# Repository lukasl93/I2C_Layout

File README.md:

# I2C_Layout
Jolla Phone Breakoutboard PCB Layout

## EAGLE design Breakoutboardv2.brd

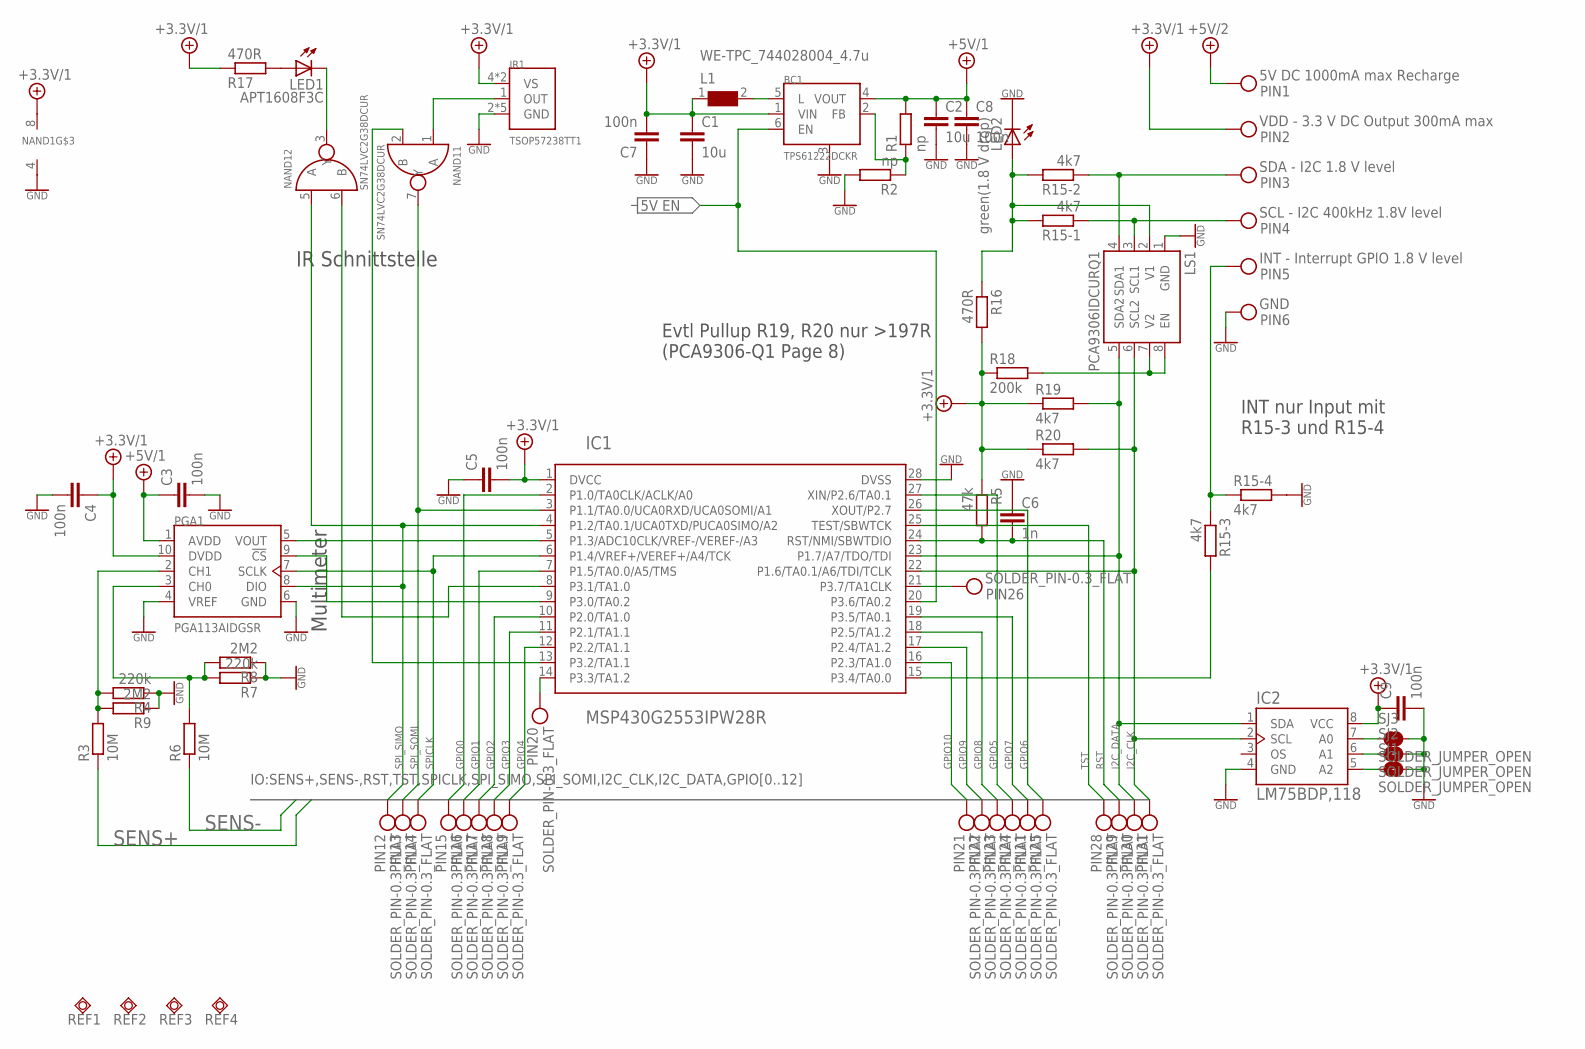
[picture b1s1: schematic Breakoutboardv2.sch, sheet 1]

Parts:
BC1: TPS61222DCKR; SOP65P210X110-6L
C1, C2: 10u; CAPC2012X95N
C3, C4, C5, C7, C8, C9: 100n; CAPC1608X90L
C6: 1n; CAPC1608X90L
IC1: MSP430G2553IPW28R; SOP65P640X120-28L
IC2: LM75BDP,118; SOP65P400X130-8L
IR1: TSOP57238TT1; TSOP572
L1: WE-TPC_744028004_4.7u; WE-TPC_2811/2813
LED1: APT1608F3C; LED-0603
LED2: green(1.8 V drop); LED-0603
LS1: PCA9306IDCURQ1; SOP50P310X90-8L
NAND1: SN74LVC2G38DCUR; SOP50P310X90-8L
PGA1: PGA113AIDGSR; SOP50P490X110-10L
PIN1: 5V DC 1000mA max Recharge; SOLDER_PIN_1_FLAT
PIN2: VDD - 3.3 V DC Output 300mA max; SOLDER_PIN_1_FLAT
PIN3: SDA - I2C 1.8 V level; SOLDER_PIN_1_FLAT
PIN4: SCL - I2C 400kHz 1.8V level; SOLDER_PIN_1_FLAT
PIN5: INT - Interrupt GPIO 1.8 V level; SOLDER_PIN_1_FLAT
PIN6: GND; SOLDER_PIN_1_FLAT
PIN11, PIN12, PIN13, PIN14, PIN15, PIN16, PIN17, PIN18, PIN19, PIN20, PIN21, PIN22, PIN23, PIN24, PIN25, PIN26, PIN28, PIN29, PIN30, PIN31: SOLDER_PIN-0.3_FLAT; SOLDER_PIN_0.3_FLAT
R1, R2: np; RESC1608X45L
R3, R6: 10M; RESC1608X45L
R4, R7: 220k; RESC1608X45L
R5: 47k; RESC1608X45L
R8, R9: 2M2; RESC1608X45L
R15: 4k7; R_ARRAY_742
R16, R17: 470R; RESC1608X45L
R18: 200k; RESC1608X45L
R19, R20: 4k7; RESC1608X45L
REF1, REF2, REF3, REF4: PCB-REF-1.27; PCB-REF
SJ1, SJ2, SJ3: SOLDER_JUMPER_OPEN; SJ-O

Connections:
5VEN: BC1.6 (EN), IC1.20 (P3.6/TA0.2)
+3.3V/1: BC1.1 (VIN), C1.1, C4.1, C5.2, C7.2, C9.1, IC1.1 (DVCC), IC2.8 (VCC), IR1.4 (VS), IR1.5 (VS), L1.1, NAND1.8 (VDD), PGA1.10 (DVDD), PIN2._, R5.1, R16.2, R17.1, R18.1, R19.1, R20.1; also elsewhere on the board
+5V/1: BC1.4 (VOUT), C2.1, C3.1, C8.1, PGA1.1 (AVDD), R1.2; also elsewhere on the board
+5V/2: PIN1._; also elsewhere on the board
CS_PGA: IC1.9 (P3.0/TA0.2), PGA1.9 (!CS)
GND: BC1.3 (GND), C1.2, C2.2, C3.2, C4.2, C5.1, C6.1, C7.1, C8.2, C9.2, IC1.28 (DVSS), IC2.4 (GND), IR1.2 (GND), IR1.3 (GND), IR1.6 (GND), IR1.7 (GND), IR1.8 (GND), LED2.C, LS1.1 (GND), NAND1.4 (GND), PGA1.4 (VREF), PGA1.6 (GND), PIN6._, R2.2, R4.1, R7.1, R8.1, R9.1, R15.5 (2), SJ1.2, SJ2.2, SJ3.2; also elsewhere on the board
GPIO0: IC1.2 (P1.0/TA0CLK/ACLK/A0), PIN15._; also elsewhere on the board
GPIO1: IC1.7 (P1.5/TA0.0/A5/TMS), PIN16._; also elsewhere on the board
GPIO2: IC1.10 (P2.0/TA1.0), PIN17._; also elsewhere on the board
GPIO3: IC1.11 (P2.1/TA1.1), PIN18._; also elsewhere on the board
GPIO4: IC1.12 (P2.2/TA1.1), PIN19._; also elsewhere on the board
GPIO5: IC1.27 (XIN/P2.6/TA0.1), PIN24._; also elsewhere on the board
GPIO6: IC1.26 (XOUT/P2.7), PIN25._; also elsewhere on the board
GPIO7: IC1.19 (P3.5/TA0.1), PIN11._; also elsewhere on the board
GPIO8: IC1.18 (P2.5/TA1.2), PIN23._; also elsewhere on the board
GPIO9: IC1.17 (P2.4/TA1.2), PIN22._; also elsewhere on the board
GPIO10: IC1.16 (P2.3/TA1.0), PIN21._; also elsewhere on the board
I2C_CLK: IC1.22 (P1.6/TA0.1/A6/TDI/TCLK), IC2.2 (SCL), LS1.6 (SCL2), PIN31._, R20.2; also elsewhere on the board
I2C_DATA: IC1.23 (P1.7/A7/TDO/TDI), IC2.1 (SDA), LS1.5 (SDA2), PIN30._, R19.2; also elsewhere on the board
INT_JOLLA: IC1.15 (P3.4/TA0.0), R15.6 (2)
IR-R_CONT: IC1.13 (P3.2/TA1.1), NAND1.2 (B)
IR-T_CONT: IC1.8 (P3.1/TA1.0), NAND1.6 (B)
unnamed: BC1.2 (FB), R1.1, R2.1
unnamed: BC1.5 (L), L1.2
unnamed: IC2.7 (A0), SJ3.1
unnamed: PGA1.2 (CH1), R3.2, R4.2, R9.2
unnamed: IC2.6 (A1), SJ2.1
unnamed: IC1.14 (P3.3/TA1.2), PIN20._
unnamed: PGA1.3 (CH0), R6.2, R7.2, R8.2
unnamed: IC2.5 (A2), SJ1.1
unnamed: IC1.21 (P3.7/TA1CLK), PIN26._
unnamed: LED1.A, R17.2
unnamed: PIN5._, R15.3 (1), R15.4 (1)
unnamed: LED2.A, LS1.2 (V1), R15.7 (2), R15.8 (2), R16.1
unnamed: IR1.1 (OUT), NAND1.1 (A)
unnamed: LED1.C, NAND1.3 (Y)
unnamed: LS1.4 (SDA1), PIN3._, R15.2 (1)
unnamed: LS1.7 (V2), LS1.8 (EN), R18.2
unnamed: LS1.3 (SCL1), PIN4._, R15.1
RST: C6.2, IC1.24 (RST/NMI/SBWTDIO), PIN29._, R5.2; also elsewhere on the board
SENS+: R3.1; also elsewhere on the board
SENS-: R6.1; also elsewhere on the board
SPICLK: IC1.6 (P1.4/VREF+/VEREF+/A4/TCK), PGA1.7 (SCLK), PIN14._; also elsewhere on the board
SPI_SIMO: IC1.4 (P1.2/TA0.1/UCA0TXD/PUCA0SIMO/A2), NAND1.5 (A), PGA1.8 (DIO), PIN12._; also elsewhere on the board
SPI_SOMI: IC1.3 (P1.1/TA0.0/UCA0RXD/UCA0SOMI/A1), NAND1.7 (Y), PIN13._; also elsewhere on the board
TST: IC1.25 (TEST/SBWTCK), PIN28._; also elsewhere on the board
VAD_SENSE: IC1.5 (P1.3/ADC10CLK/VREF-/VEREF-/A3), PGA1.5 (VOUT)

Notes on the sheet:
Evtl Pullup R19, R20 nur >197R (PCA9306-Q1 Page 8)
INT nur Input mit R15-3 und R15-4
IR Schnittstelle
Multimeter

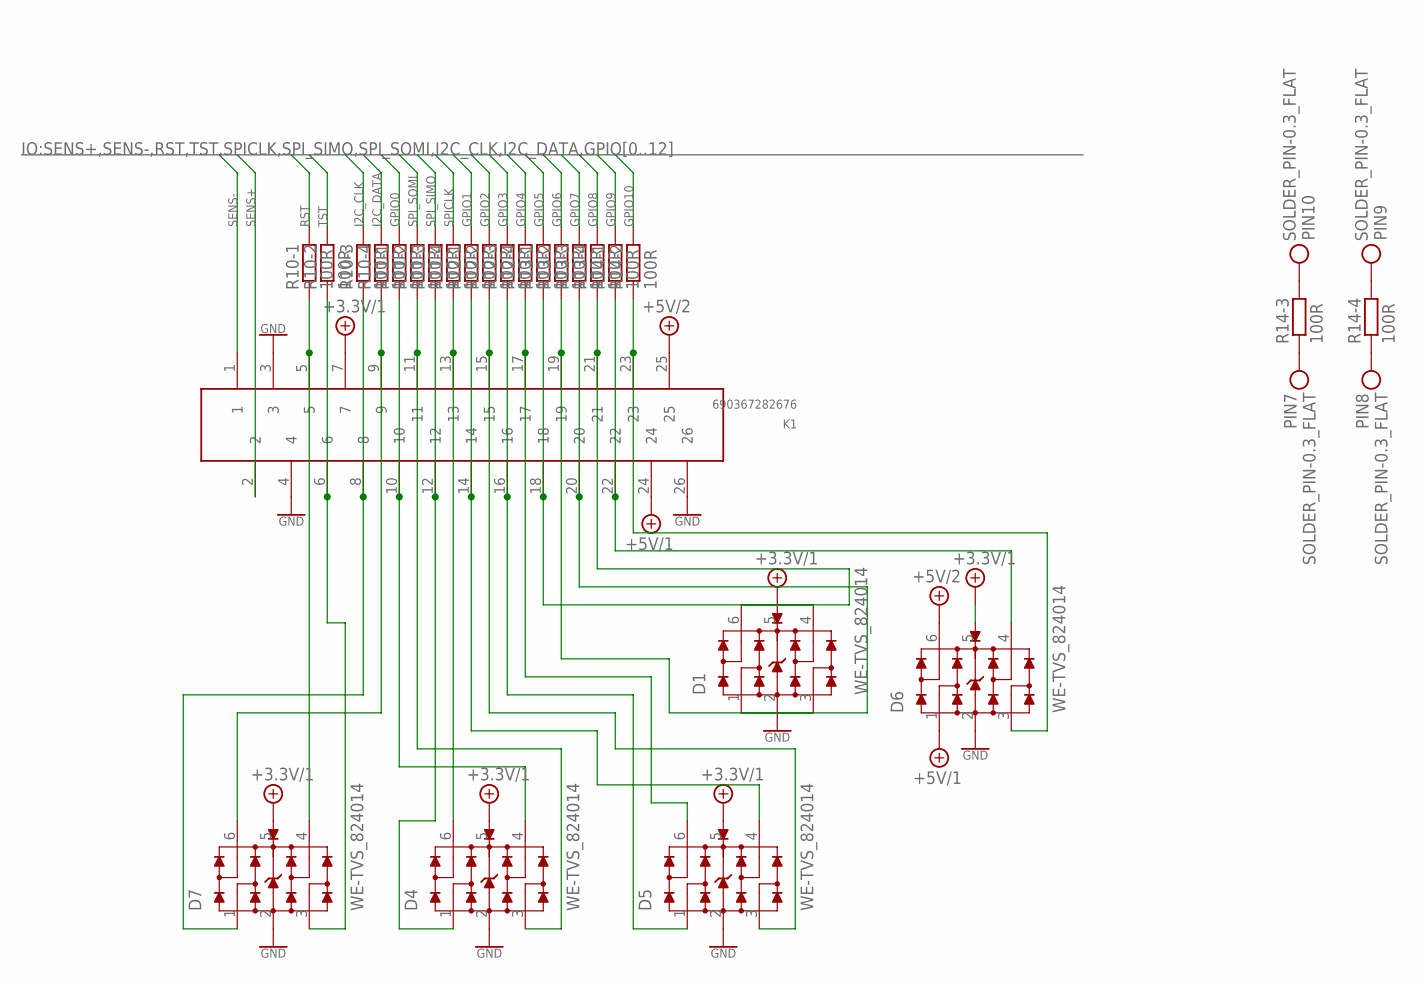
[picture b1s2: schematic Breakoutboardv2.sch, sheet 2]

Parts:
D1, D4, D5, D6, D7: WE-TVS_824014; WE-TVS_SOT23-6L
K1: 690367282676
PIN7, PIN8, PIN9, PIN10: SOLDER_PIN-0.3_FLAT; SOLDER_PIN_0.3_FLAT
R10, R11, R12, R13, R14: 100R; R_ARRAY_742

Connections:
+3.3V/1: D1.5 (VDD), D4.5 (VDD), D5.5 (VDD), D6.5 (VDD), D7.5 (VDD), K1.7; also elsewhere on the board
+5V/1: D6.1, K1.24; also elsewhere on the board
+5V/2: D6.6 (4), K1.25; also elsewhere on the board
GND: D1.2 (GND), D4.2 (GND), D5.2 (GND), D6.2 (GND), D7.2 (GND), K1.3, K1.4, K1.26; also elsewhere on the board
GPIO0: R11.8 (2); also elsewhere on the board
GPIO1: R12.8 (2); also elsewhere on the board
GPIO2: R12.7 (2); also elsewhere on the board
GPIO3: R12.6 (2); also elsewhere on the board
GPIO4: R12.5 (2); also elsewhere on the board
GPIO5: R13.8 (2); also elsewhere on the board
GPIO6: R13.7 (2); also elsewhere on the board
GPIO7: R13.6 (2); also elsewhere on the board
GPIO8: R13.5 (2); also elsewhere on the board
GPIO9: R14.8 (2); also elsewhere on the board
GPIO10: R14.7 (2); also elsewhere on the board
I2C_CLK: R10.6 (2); also elsewhere on the board
I2C_DATA: R10.5 (2); also elsewhere on the board
unnamed: D7.1, K1.8, R10.3 (1)
unnamed: D7.6 (4), K1.9, R10.4 (1)
unnamed: D4.4 (3), K1.10, R11.1
unnamed: D4.1, K1.12, R11.3 (1)
unnamed: D4.6 (4), K1.13, R11.4 (1)
unnamed: D5.4 (3), K1.14, R12.1
unnamed: D5.3 (2), K1.15, R12.2 (1)
unnamed: D5.1, K1.16, R12.3 (1)
unnamed: D7.4 (3), K1.5, R10.1
unnamed: D7.3 (2), K1.6, R10.2 (1)
unnamed: D4.3 (2), K1.11, R11.2 (1)
unnamed: D5.6 (4), K1.17, R12.4 (1)
unnamed: D1.4 (3), K1.18, R13.1
unnamed: D1.3 (2), K1.19, R13.2 (1)
unnamed: D1.1, K1.20, R13.3 (1)
unnamed: D1.6 (4), K1.21, R13.4 (1)
unnamed: D6.4 (3), K1.22, R14.1
unnamed: D6.3 (2), K1.23, R14.2 (1)
unnamed: PIN7._, R14.3 (1)
unnamed: PIN8._, R14.4 (1)
unnamed: PIN9._, R14.5 (2)
unnamed: PIN10._, R14.6 (2)
RST: R10.8 (2); also elsewhere on the board
SENS+: K1.2; also elsewhere on the board
SENS-: K1.1; also elsewhere on the board
SPICLK: R11.5 (2); also elsewhere on the board
SPI_SIMO: R11.6 (2); also elsewhere on the board
SPI_SOMI: R11.7 (2); also elsewhere on the board
TST: R10.7 (2); also elsewhere on the board

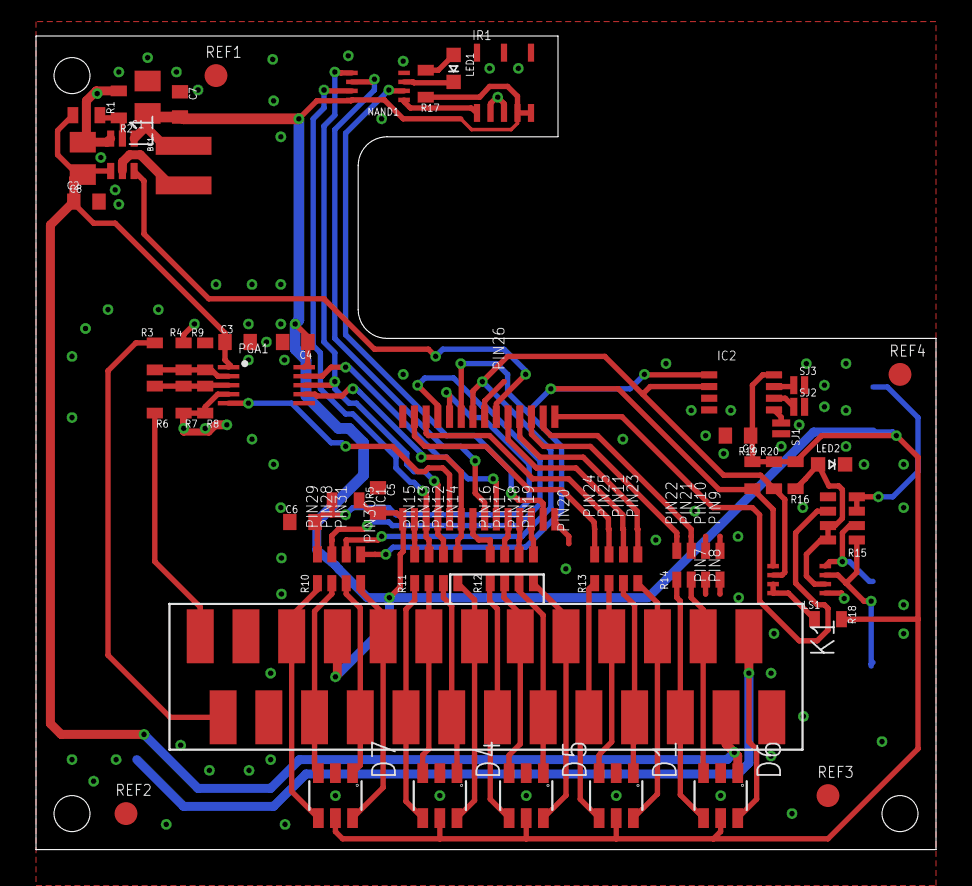
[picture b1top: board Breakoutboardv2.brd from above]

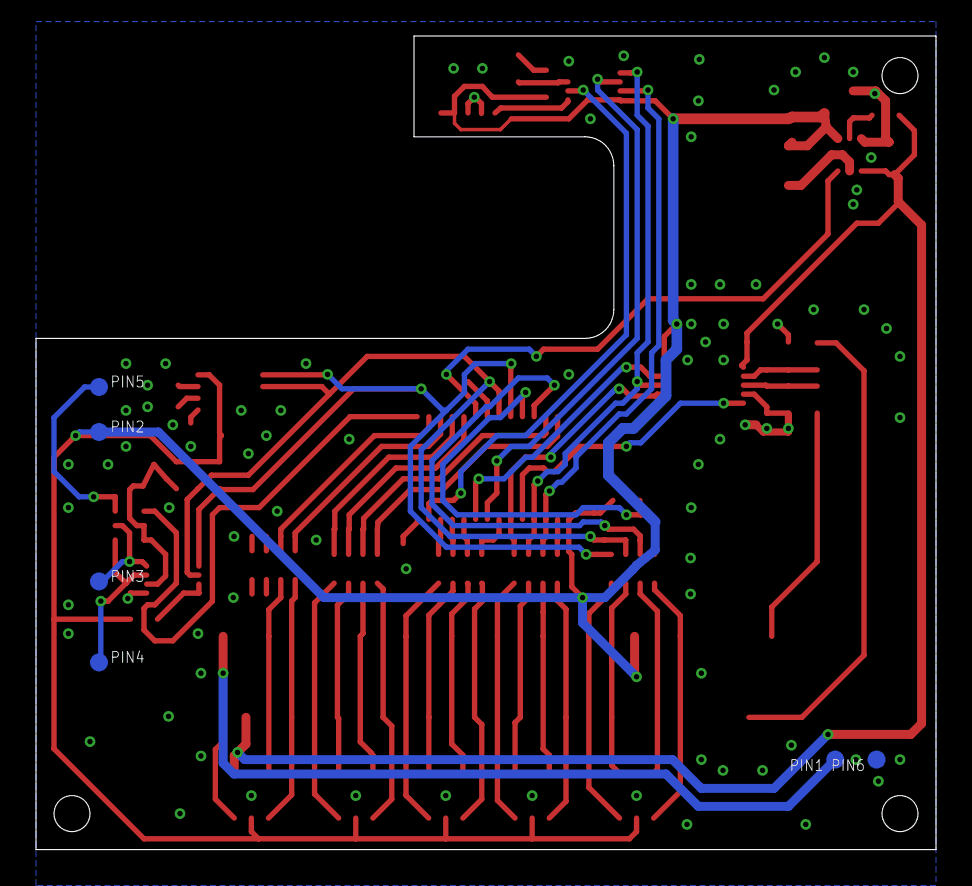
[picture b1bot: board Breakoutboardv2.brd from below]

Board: 2 copper layers, 50.0 x 45.2 mm, 82 parts (6 on the bottom side), 69 nets.

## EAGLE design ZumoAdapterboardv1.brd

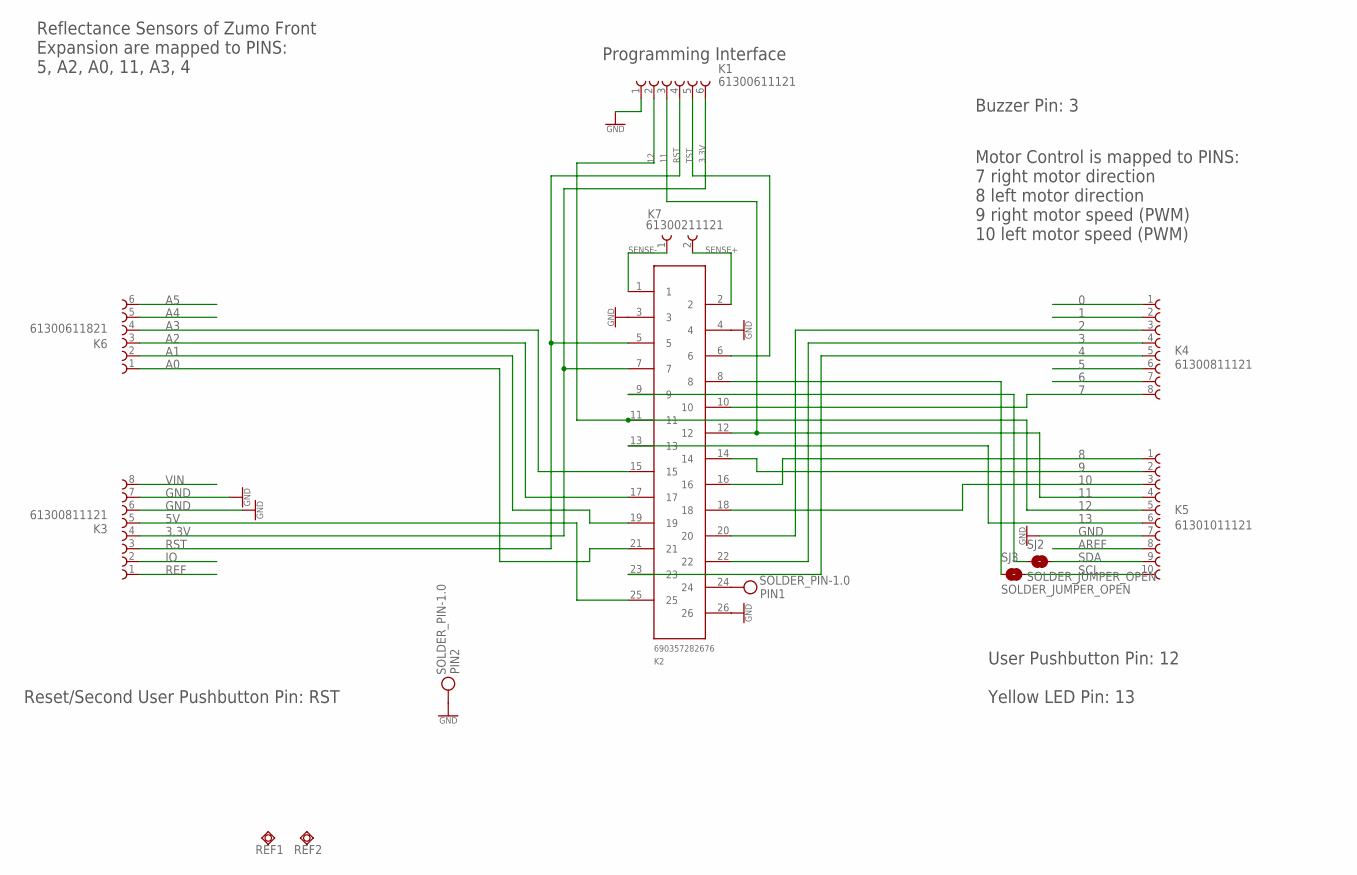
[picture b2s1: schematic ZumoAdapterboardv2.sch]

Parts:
K1: 61300611121
K2: 690357282676
K3, K4: 61300811121
K5: 61301011121
K6: 61300611821
K7: 61300211121
PIN1, PIN2: SOLDER_PIN-1.0; SOLDER_PIN_1.0
REF1, REF2: PCB-REF-1.27; PCB-REF
SJ2, SJ3: SOLDER_JUMPER_OPEN; SJ-O

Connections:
0: K4.1
1: K4.2
2: K2.20, K4.3
3: K2.22, K4.4
3.3V: K1.6, K2.7, K3.4
4: K2.23, K4.5
5: K4.6
5V: K2.25, K3.5
6: K4.7
7: K2.10, K4.8
8: K2.16, K5.1
9: K2.14, K5.2
10: K2.18, K5.3
11: K1.3, K2.12, K5.4
12: K1.2, K2.11, K5.5
13: K2.13, K5.6
A0: K2.21, K6.1
A1: K2.19, K6.2
A2: K2.17, K6.3
A3: K2.15, K6.4
A4: K6.5
A5: K6.6
AREF: K5.8
GND: K1.1, K2.3, K2.4, K2.26, K3.6, K3.7, K5.7, PIN2._
IO: K3.2
unnamed: K2.24, PIN1._
unnamed: K2.8, SJ3.1
unnamed: K2.9, SJ2.1
REF: K3.1
RST: K1.4, K2.5, K3.3
SCL: K5.10, SJ3.2
SDA: K5.9, SJ2.2
SENSE+: K2.2, K7.2
SENSE-: K2.1, K7.1
TST: K1.5, K2.6
VIN: K3.8

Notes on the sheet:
Reflectance Sensors of Zumo Front Expansion are mapped to PINS: 5, A2, A0, 11, A3, 4
Motor Control is mapped to PINS: 7 right motor direction 8 left motor direction 9 right motor speed (PWM) 10 left motor speed (PWM)
Buzzer Pin: 3
Yellow LED Pin: 13
User Pushbutton Pin: 12
Reset/Second User Pushbutton Pin: RST
Programming Interface

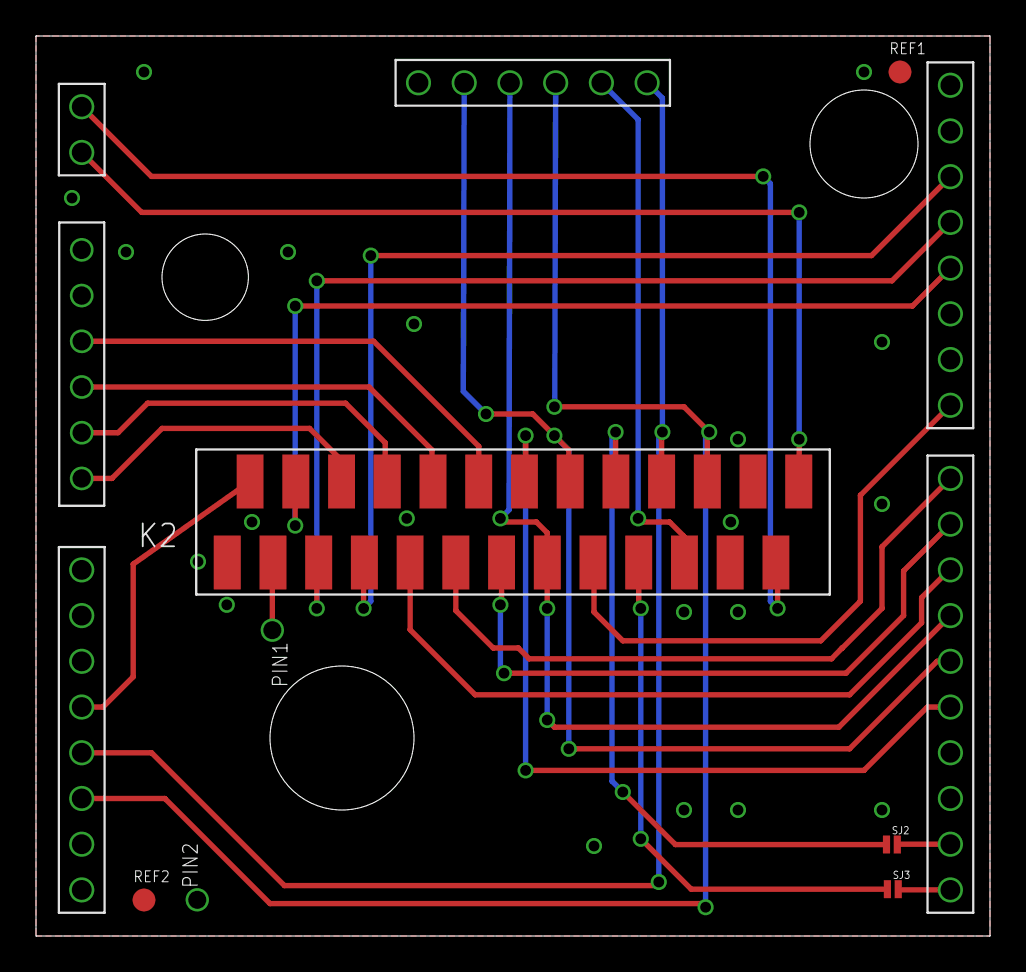
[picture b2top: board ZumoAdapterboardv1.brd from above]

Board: 2 copper layers, 53.0 x 50.0 mm, 13 parts (0 on the bottom side), 26 nets.

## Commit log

2015-08-23 Initial commit of Breakoutboard and Adapterboard layouts in Version 1.0

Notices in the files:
parts and their libraries:
MasterPhonebot: Created A. Bachmaier, K&K Prime Engineering GmbH (c) 2011
